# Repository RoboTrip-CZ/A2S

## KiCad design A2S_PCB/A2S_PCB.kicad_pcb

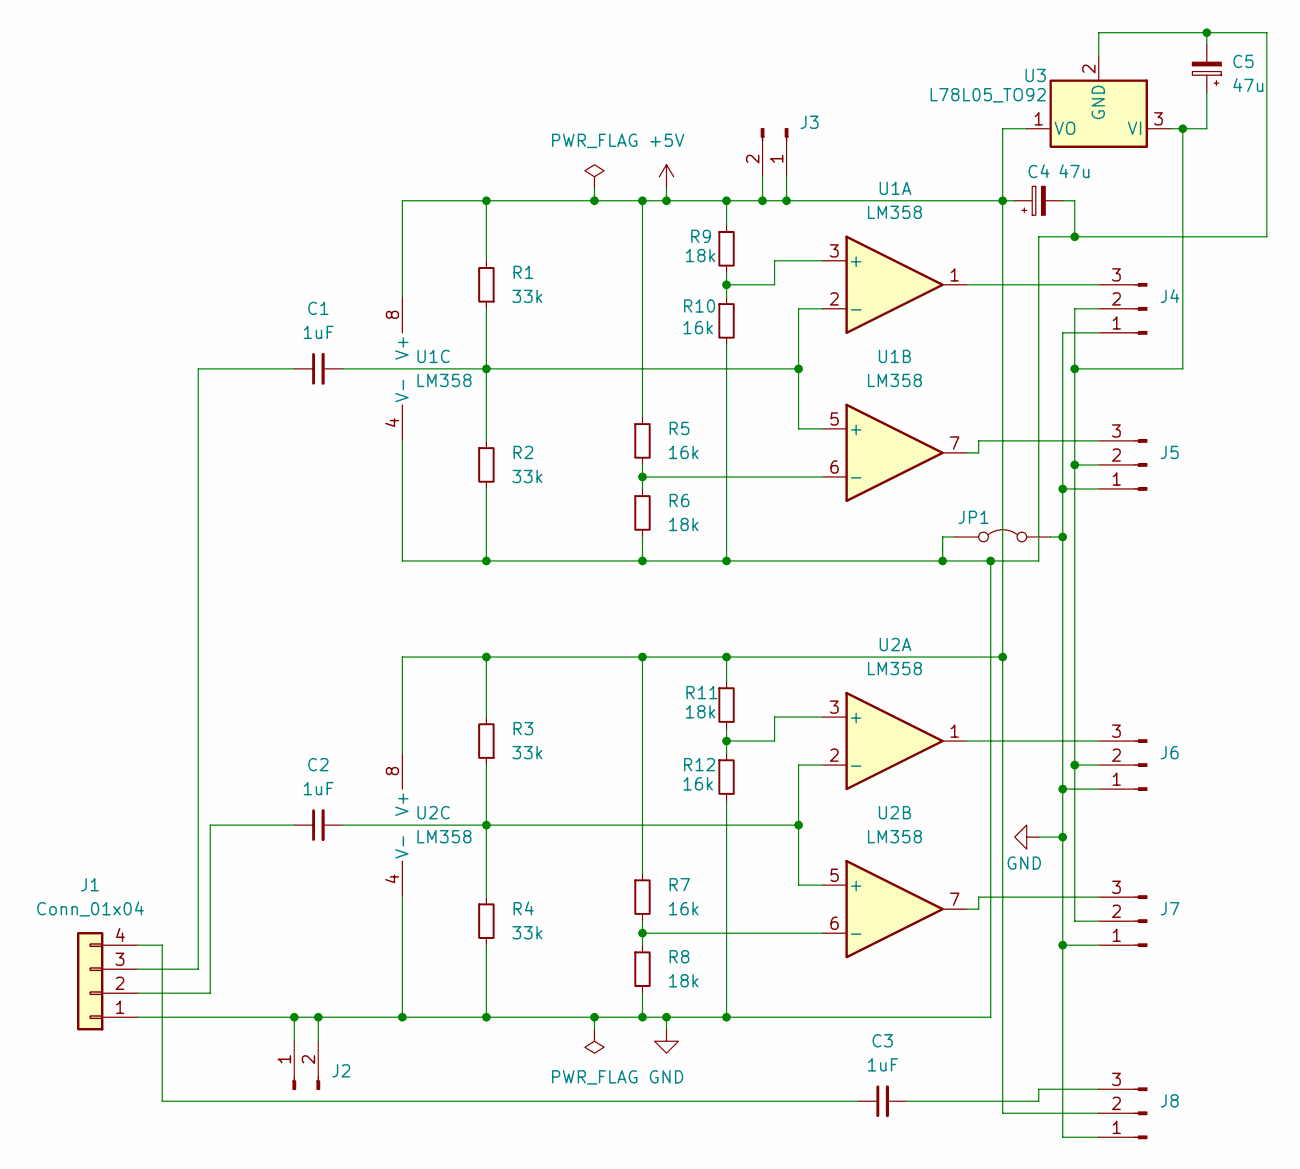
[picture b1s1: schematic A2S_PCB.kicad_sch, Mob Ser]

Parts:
C1, C2, C3: 1uF; C_Disc_D8.0mm_W2.5mm_P5.00mm
C4, C5: 47u; CP_Radial_D4.0mm_P2.00mm
J1: Conn_01x04; FanPinHeader_1x04_P2.54mm_Vertical
J2: Conn_01x02_Pin; PinHeader_1x02_P2.54mm_Vertical
J3: PinHeader_1x02_P2.54mm_Vertical
J4, J5, J6, J7: PinHeader_1x03_P2.54mm_Vertical
J8: Conn_01x03_Pin; PinHeader_1x03_P2.54mm_Vertical
JP1: TestPoint_2Pads_Pitch2.54mm_Drill0.8mm
R1, R2, R3, R4: 33k; R_Axial_DIN0204_L3.6mm_D1.6mm_P7.62mm_Horizontal
R5, R7, R10, R12: 16k; R_Axial_DIN0204_L3.6mm_D1.6mm_P7.62mm_Horizontal
R6, R8, R9, R11: 18k; R_Axial_DIN0204_L3.6mm_D1.6mm_P7.62mm_Horizontal
U1, U2: LM358; DIP-8_W7.62mm_LongPads
U3: L78L05_TO92; TO-92L_Inline_Wide

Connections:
+5V: C4.1, J3.1, J3.2, J8.2, R1.2, R3.2, R5.1, R7.1, R9.1, R11.1, U1.8 (V+), U2.8 (V+), U3.1 (VO)
GND: C4.2, C5.2, J1.1, J2.1, J2.2, J4.1, J5.1, J6.1, J7.1, J8.1, JP1.1 (A), JP1.2 (B), R2.2, R4.2, R6.2, R8.2, R10.2, R12.2, U1.4 (V-), U2.4 (V-), U3.2 (GND)
unnamed: C2.1, J1.2
unnamed: C1.1, J1.3
unnamed: C3.1, J1.4
unnamed: C5.1, J4.2, J5.2, J6.2, J7.2, U3.3 (VI)
unnamed: J4.3, U1.1
unnamed: J5.3, U1.7
unnamed: J6.3, U2.1
unnamed: J7.3, U2.7
unnamed: C3.2, J8.3
unnamed: R9.2, R10.1, U1.3 (+)
unnamed: C1.2, R1.1, R2.1, U1.2 (-), U1.5 (+)
unnamed: R5.2, R6.1, U1.6 (-)
unnamed: R11.2, R12.1, U2.3 (+)
unnamed: C2.2, R3.1, R4.1, U2.2 (-), U2.5 (+)
unnamed: R7.2, R8.1, U2.6 (-)

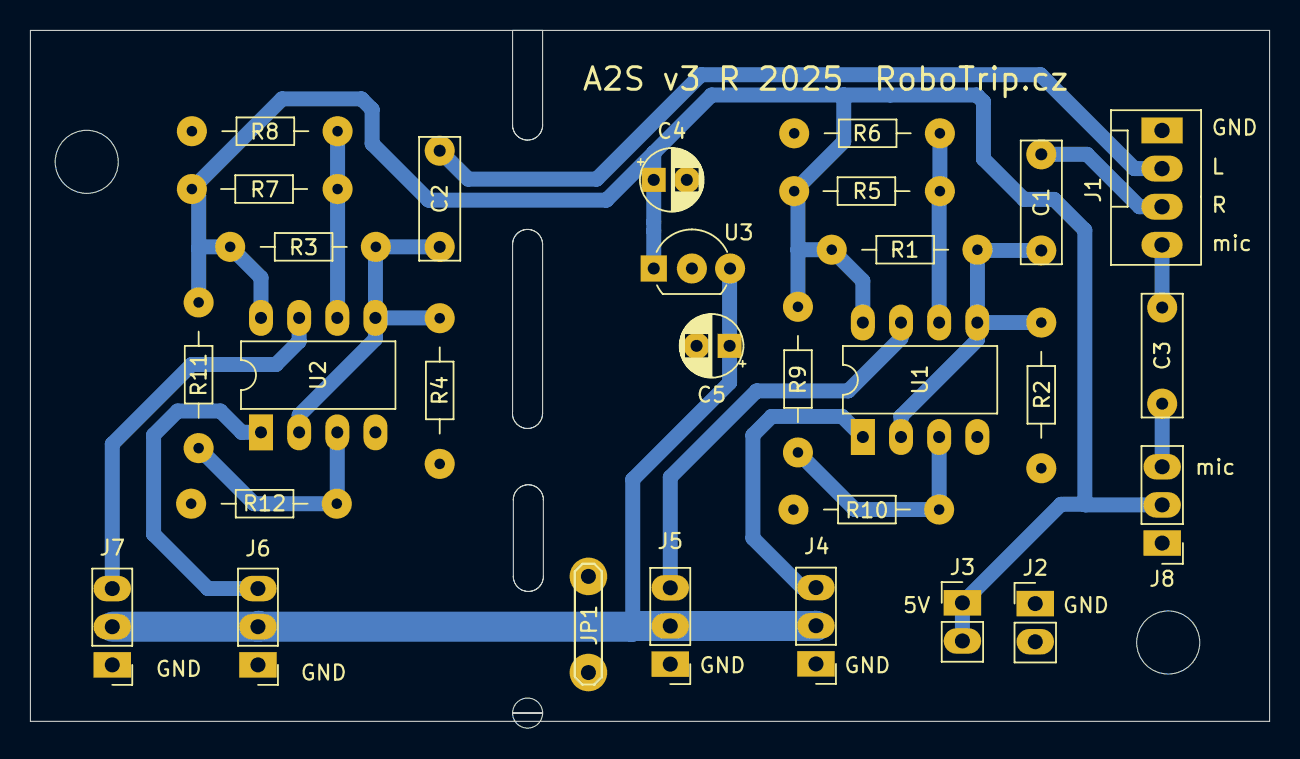
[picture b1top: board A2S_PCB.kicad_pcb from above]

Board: 2 copper layers, 82.5 x 46.5 mm, 29 parts (0 on the bottom side), 17 nets.

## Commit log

2026-03-28 Create LICENSE
2026-04-07 Create PCB
